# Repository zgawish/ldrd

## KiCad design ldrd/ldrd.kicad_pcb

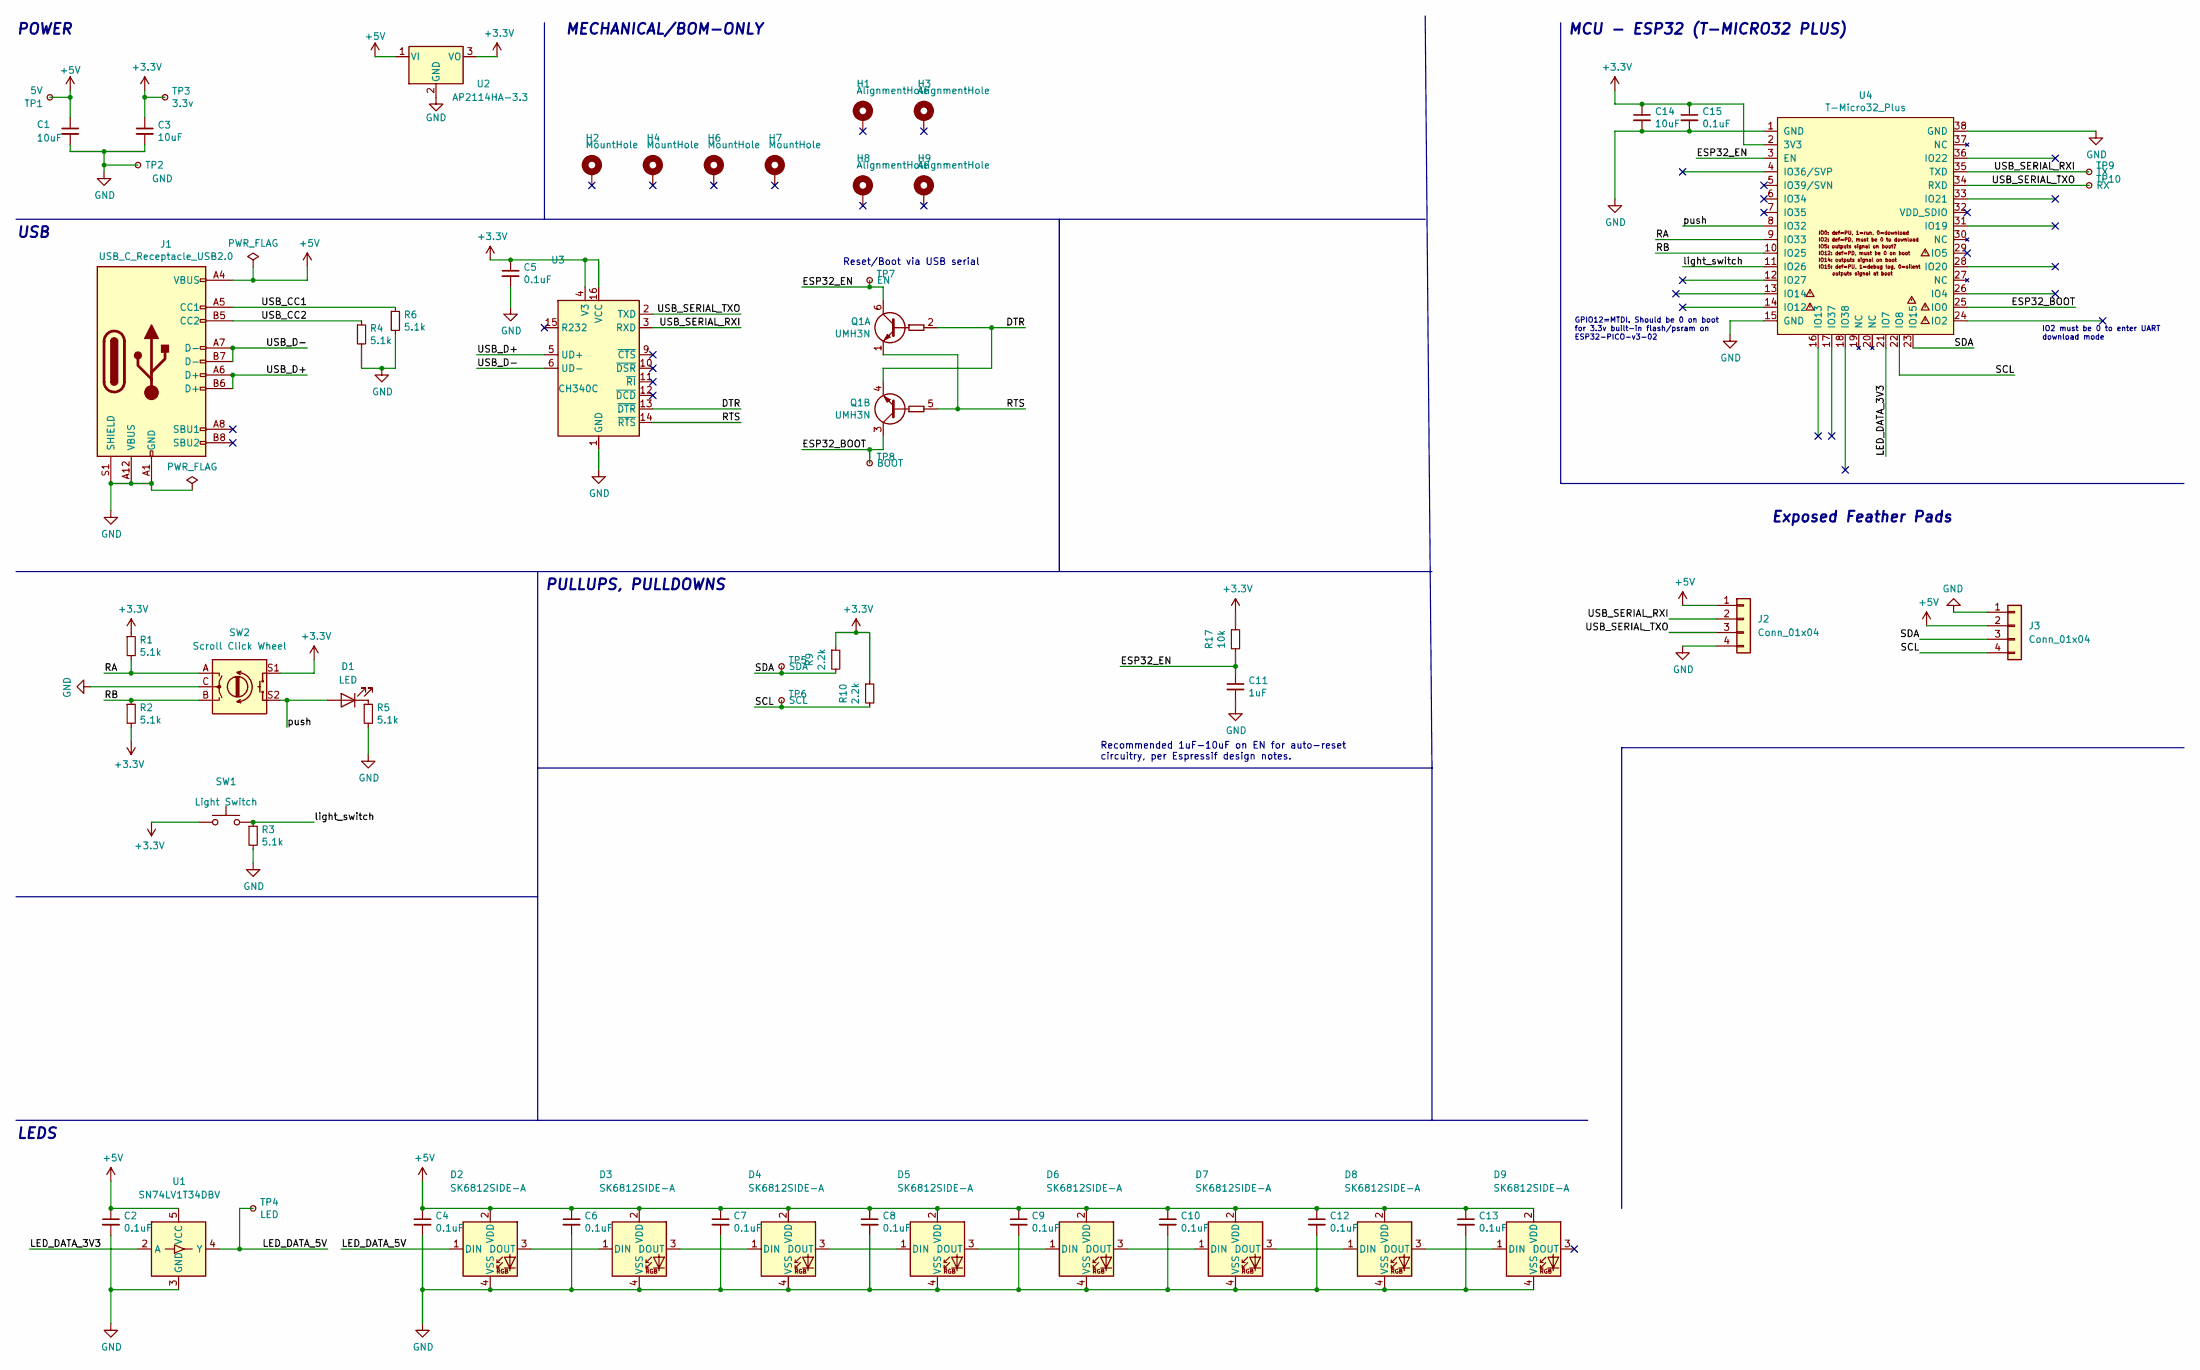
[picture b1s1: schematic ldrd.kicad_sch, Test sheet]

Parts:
C1, C3, C14: 10uF; C_0805_2012Metric; LCSC C2922480
C2, C4, C5, C6, C7, C8, C9, C10, C12, C13, C15: 0.1uF; C_0603_1608Metric; LCSC C1591
C11: 1uF; C_0603_1608Metric; Mouser 187-CL10A105KA8NNNC
D1: LED; LED_D5.0mm_Horizontal_O1.27mm_Z15.0mm
D2, D3, D4, D5, D6, D7, D8, D9: SK6812SIDE-A; SK6812-SIDE-A; Digikey 1528-4691-ND
H1, H3, H8, H9: AlignmentHole; MountingHole_2.2mm_M2_ISO7380_Pad_NonVirtual
H2, H4, H6, H7: MountHole; MountingHole_2.2mm_M2_ISO7380_Pad_NonVirtual
J1: USB_C_Receptacle_USB2.0; USB_C_Receptacle_XKB_U262-161N-4BVC11; LCSC C428463
J2, J3: Conn_01x04; PinHeader_1x04_P2.54mm_Vertical
Q1: UMH3N; SOT-363_SC-70-6; LCSC C62892
R1, R2, R3, R4, R5, R6: 5.1k; R_0603_1608Metric; LCSC C105580
R9, R10: 2.2k; R_0603_1608Metric; LCSC C4190
R17: 10k; R_0603_1608Metric; LCSC C98220
SW1: Light Switch; SW_PUSH_6mm_H4.3mm
SW2: Scroll Click Wheel; RotaryEncoder_Alps_EC11E-Switch_Vertical_H20mm
TP1: 5V; TestPoint_Pad_D2.0mm_ValueSilk
TP2: GND; TestPoint_Pad_D2.0mm_ValueSilk
TP3: 3.3v; TestPoint_Pad_D2.0mm_ValueSilk
TP4: LED; TestPoint_Pad_D2.0mm_ValueSilk
TP5: SDA; TestPoint_Pad_D2.0mm_ValueSilk
TP6: SCL; TestPoint_Pad_D2.0mm_ValueSilk
TP7: EN; TestPoint_Pad_D2.0mm_ValueSilk
TP8: BOOT; TestPoint_Pad_D2.0mm_ValueSilk
TP9: TX; TestPoint_Pad_D2.0mm_ValueSilk
TP10: RX; TestPoint_Pad_D2.0mm_ValueSilk
U1: SN74LV1T34DBV; SOT-23-5; LCSC C100024
U2: AP2114HA-3.3; SOT-223-3_TabPin2; LCSC C460314
U3: CH340C; SOIC-16_3.9x9.9mm_P1.27mm; LCSC C84681
U4: T-Micro32_Plus; T-Micro32; Digikey N/A

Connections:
+3V3: C3.1, C5.1, C14.1, C15.1, R1.1, R2.2, R9.1, R10.1, R17.1, SW1.1, SW2.S1, TP3.1, U2.3 (VO), U3.4 (V3), U3.16 (VCC), U4.2 (3V3)
+5V: C1.1, C2.1, C4.1, C6.1, C7.1, C8.1, C9.1, C10.1, C12.1, C13.1, D2.2 (VDD), D3.2 (VDD), D4.2 (VDD), D5.2 (VDD), D6.2 (VDD), D7.2 (VDD), D8.2 (VDD), D9.2 (VDD), J1.A4 (VBUS), J1.A9 (VBUS), J2.1, J3.2, TP1.1, U1.5 (VCC), U2.1 (VI)
/DTR: Q1.2 (B1), Q1.4 (E2), U3.13 (~DTR)
/ESP32_BOOT: Q1.3 (C2), TP8.1, U4.25 (IO0)
/ESP32_EN: C11.1, Q1.6 (C1), R17.2, TP7.1, U4.3 (EN)
/LED_DATA_3V3: U1.2 (A), U4.21 (IO7)
/LED_DATA_5V: D2.1 (DIN), TP4.1, U1.4 (Y)
/RA: R1.2, SW2.A, U4.9 (IO33)
/RB: R2.1, SW2.B, U4.10 (IO25)
/RTS: Q1.1 (E1), Q1.5 (B2), U3.14 (~RTS)
/SCL: J3.4, R10.2, TP6.1, U4.22 (IO8)
/SDA: J3.3, R9.2, TP5.1, U4.23 (IO15)
/USB_CC1: J1.A5 (CC1), R6.1
/USB_CC2: J1.B5 (CC2), R4.1
/USB_D+: J1.A6 (D+), J1.B6 (D+), U3.5 (UD+)
/USB_D-: J1.A7 (D-), J1.B7 (D-), U3.6 (UD-)
/USB_SERIAL_RXI: J2.2, TP9.1, U3.3 (RXD), U4.35 (TXD)
/USB_SERIAL_TXO: J2.3, TP10.1, U3.2 (TXD), U4.34 (RXD)
/light_switch: R3.1, SW1.2, U4.11 (IO26)
/push: D1.2 (A), SW2.S2, U4.8 (IO32)
GND: C1.2, C2.2, C3.2, C4.2, C5.2, C6.2, C7.2, C8.2, C9.2, C10.2, C11.2, C12.2, C13.2, C14.2, C15.2, D2.4 (VSS), D3.4 (VSS), D4.4 (VSS), D5.4 (VSS), D6.4 (VSS), D7.4 (VSS), D8.4 (VSS), D9.4 (VSS), J1.A1 (GND), J1.A12 (VBUS), J1.S1 (SHIELD), J2.4, J3.1, R3.2, R4.2, R5.2, R6.2, SW2.C, TP2.1, U1.3 (GND), U2.2 (GND), U3.1 (GND), U4.1 (GND), U4.15 (GND), U4.38 (GND)
unnamed: D1.1 (K), R5.1
unnamed: D2.3 (DOUT), D3.1 (DIN)
unnamed: D3.3 (DOUT), D4.1 (DIN)
unnamed: D4.3 (DOUT), D5.1 (DIN)
unnamed: D5.3 (DOUT), D6.1 (DIN)
unnamed: D6.3 (DOUT), D7.1 (DIN)
unnamed: D7.3 (DOUT), D8.1 (DIN)
unnamed: D8.3 (DOUT), D9.1 (DIN)

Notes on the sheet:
POWER
Reset/Boot via USB serial
PULLUPS, PULLDOWNS
IO2 must be 0 to enter UART download mode
MCU - ESP32 (T-MICRO32 PLUS)
GPIO12=MTDI. Should be 0 on boot for 3.3v built-in flash/psram on ESP32-PICO-v3-02
Recommended 1uF-10uF on EN for auto-reset circuitry, per Espressif design notes.
LEDS
USB
MECHANICAL/BOM-ONLY
Exposed Feather Pads

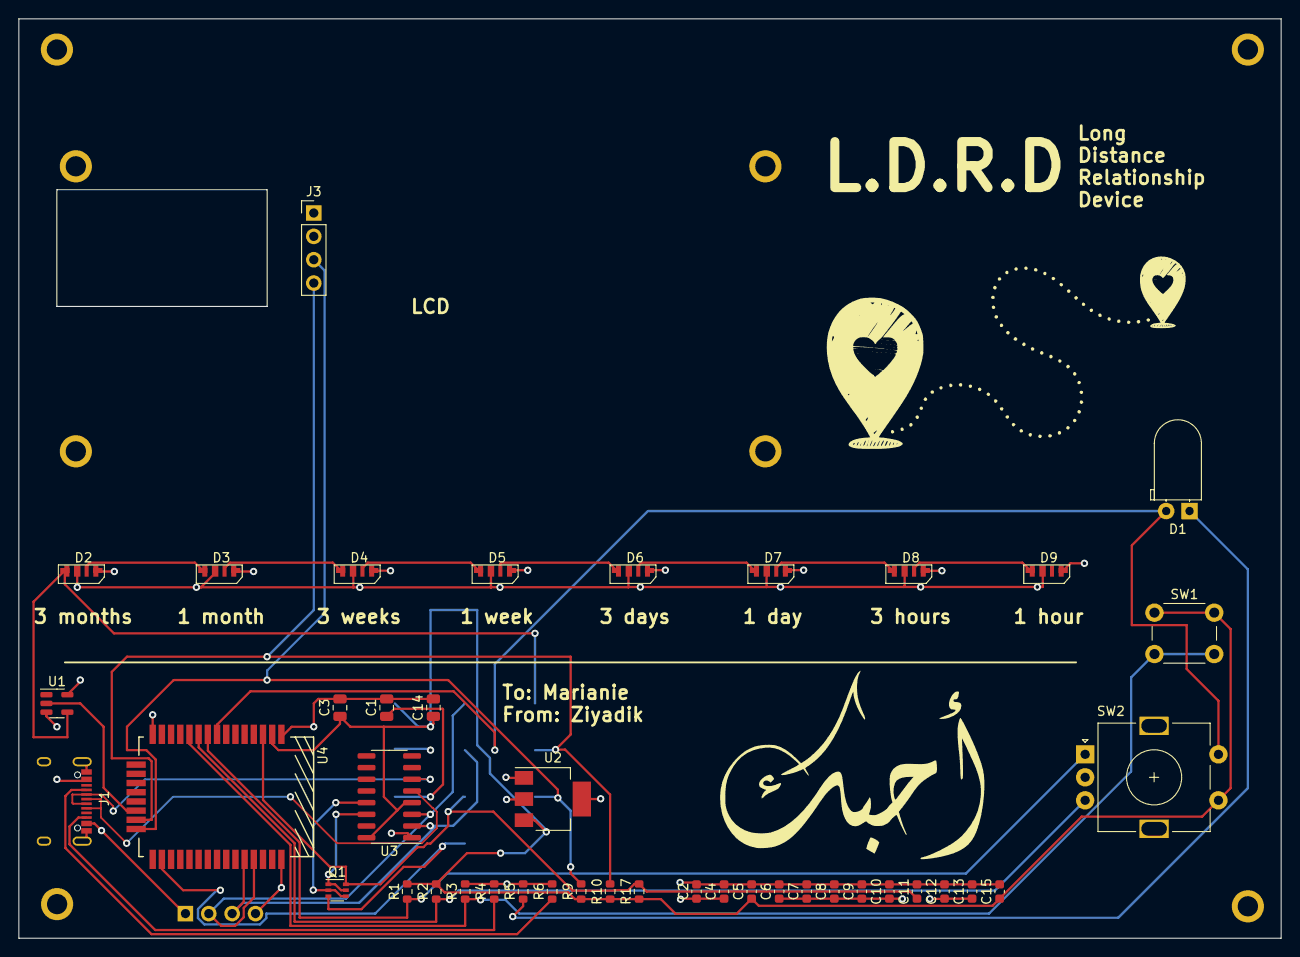
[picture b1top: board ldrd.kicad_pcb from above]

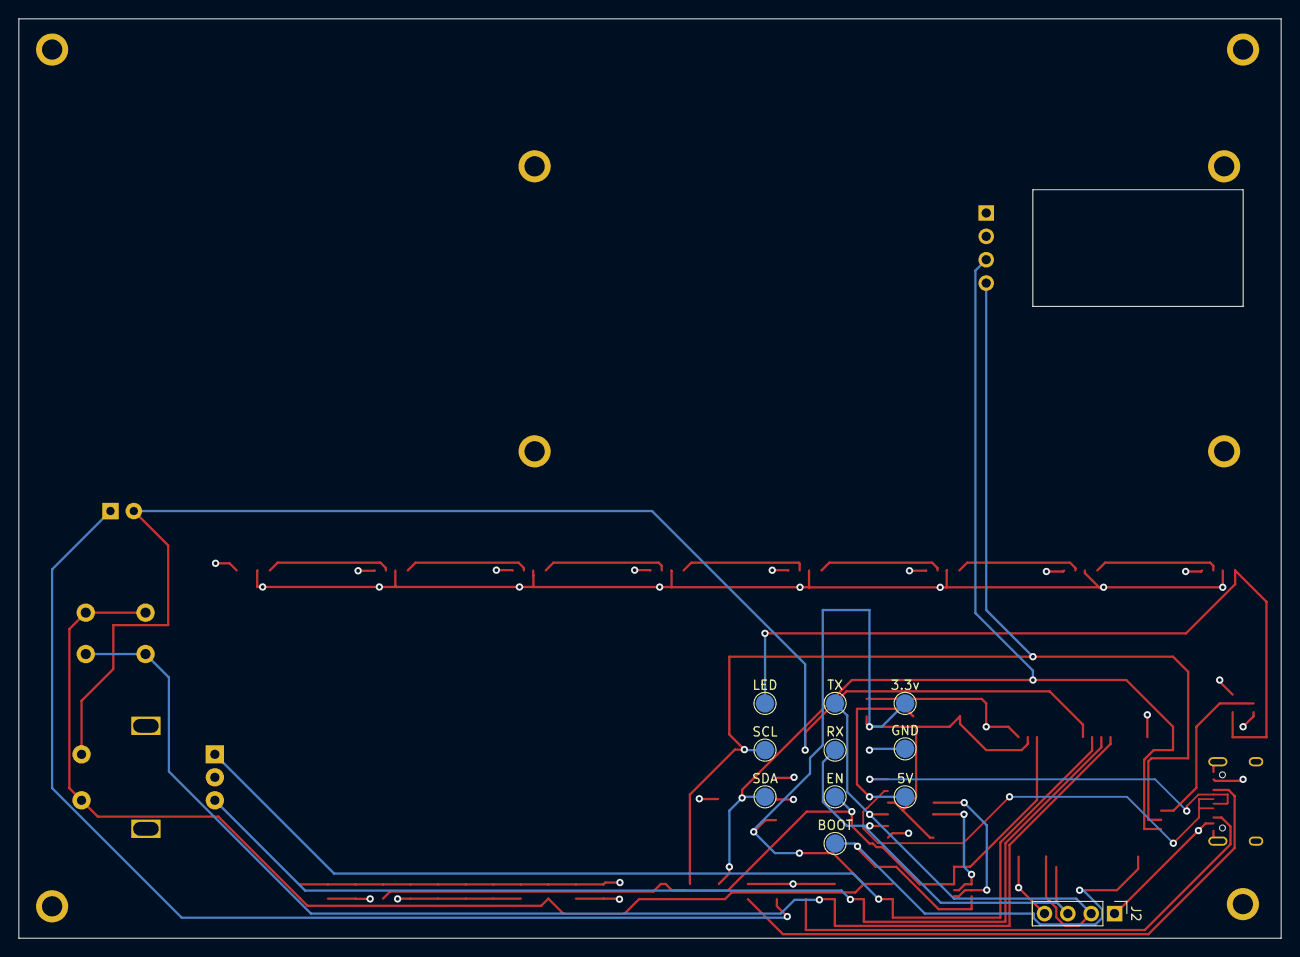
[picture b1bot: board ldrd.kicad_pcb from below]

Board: 4 copper layers, 137.3 x 100.0 mm, 61 parts (11 on the bottom side), 29 nets.

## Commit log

2023-04-26 init
2023-04-26 gerber and drill files
2023-04-27 add lcd label
2023-05-04 inner layer text + LCD label
2023-05-04 save changes after adding inner layers
2023-11-21 init firmware
